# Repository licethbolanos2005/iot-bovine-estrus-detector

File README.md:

# 🐄 IoT Bovine Estrus Detector

Prototipo IoT basado en tecnología **LoRa** para la detección temprana del celo en bovinos mediante el monitoreo continuo de variables fisiológicas y comportamentales.

> Proyecto integrador — Ingeniería Electrónica  
> Unidad Central del Valle del Cauca - Semestre 8
> Autores: Liceth Bolaños, Santiago Albarracin, Arlyn Cardozo, Samuel Guevara

---

## 📋 Descripción general

El sistema integra un nodo transmisor montado en un chaleco portador adaptado al animal, el cual captura temperatura corporal, actividad motora, frecuencia respiratoria y eventos de monta. Los datos son procesados por un **ESP32 LoRa V3 (ESP32-S3 + SX1262)**, almacenados localmente en MicroSD con marca temporal RTC y transmitidos de forma inalámbrica al nodo receptor, donde son visualizados en **Grafana** a través de **InfluxDB**.

---

## 📁 Estructura del repositorio

```
iot-bovine-estrus-detector/
│
├── Board/                  # Diseño final de la PCB (KiCad)
│   └── ...                 # Archivos .kicad_pcb, .kicad_sch, Gerbers
│
├── Box/                    # Diseño de la caja de protección (impresión 3D)
│   └── ...                 # Archivos .ipt
│
├── Receiver_Code/          # Firmware del nodo receptor
│   └── ...                 # Código ESP32 — recepción LoRa, envío a InfluxDB
│
├── Schematic/              # Esquemático electrónico del sistema
│   └── ...                 # Archivos .kicad_sch
│
├── Transmitter_Code/       # Firmware del nodo transmisor
│   └── ...                 # Código ESP32 — sensores, LoRa, MicroSD, RTC, Web server
│
└── README.md
```

---

## ⚙️ Hardware utilizado

| Componente | Función |
|---|---|
| WiFi LoRa 32 V3 (ESP32-S3 + SX1262) | Unidad central de procesamiento y comunicación |
| DS18B20 | Medición de temperatura corporal |
| MPU6050 | Actividad motora y frecuencia respiratoria |
| FSR (Force Sensitive Resistor) | Detección de eventos de monta |
| INA219 | Monitoreo de consumo energético |
| DS3231 (RTC) | Registro temporal de datos |
| Módulo MicroSD TF | Almacenamiento local de datos |
| Batería LiPo 3.7V | Alimentación del sistema |

---

## 📡 Parámetros de comunicación LoRa

| Parámetro | Valor |
|---|---|
| Banda | 915 MHz (ISM) |
| Spreading Factor | 7 |
| Bandwidth | 125 kHz |
| Coding Rate | 5 |
| Sync Word | 0x12 |
| Potencia TX | 14 dBm |

---

## 🖥️ Arquitectura del sistema

```
[Sensores] → [ESP32 Transmisor] → [LoRa 915 MHz] → [ESP32 Receptor]
                    ↓                                        ↓
               [MicroSD + RTC]                        [InfluxDB → Grafana]
                    ↓
             [Servidor Web Embebido / OTA]
```

---

## 🚀 Primeros pasos

### Requisitos

- [Arduino IDE](https://www.arduino.cc/en/software) o [PlatformIO](https://platformio.org/)
- Placa: **Heltec WiFi LoRa 32 V3**
- Librerías necesarias:
  - `RadioLib`
  - `OneWire` + `DallasTemperature`
  - `MPU6050`
  - `RTClib`
  - `SD`
  - `INA219`
  - `ArduinoJson`
  - `ESPAsyncWebServer`

### Cargar firmware transmisor

1. Abre `Transmitter_Code/` en Arduino IDE o PlatformIO.
2. Configura los parámetros de red WiFi y LoRa en el archivo de configuración.
3. Compila y carga en la placa ESP32 del nodo transmisor.

### Cargar firmware receptor

1. Abre `Receiver_Code/` en Arduino IDE o PlatformIO.
2. Configura la dirección IP de InfluxDB y las credenciales de red.
3. Compila y carga en la placa ESP32 del nodo receptor.

---

## 📊 Visualización

Los datos son enviados a **InfluxDB** y visualizados en tiempo real mediante **Grafana**, donde se monitorean:

- Temperatura corporal (°C)
- Magnitud de aceleración (actividad motora)
- Frecuencia respiratoria
- Consumo energético (mA)
- Estado de celo (algoritmo de detección)
- Eventos de monta (FSR)
- Calidad del enlace LoRa (RSSI / SNR)

---

## 🌐 Servidor web embebido

El nodo transmisor implementa un servidor web accesible en la red local mediante:

```
http://boviot.local
```

Desde la interfaz web es posible:
- Visualizar variables fisiológicas en tiempo real
- Configurar parámetros de red WiFi
- Actualizar el firmware de forma inalámbrica (**OTA**)

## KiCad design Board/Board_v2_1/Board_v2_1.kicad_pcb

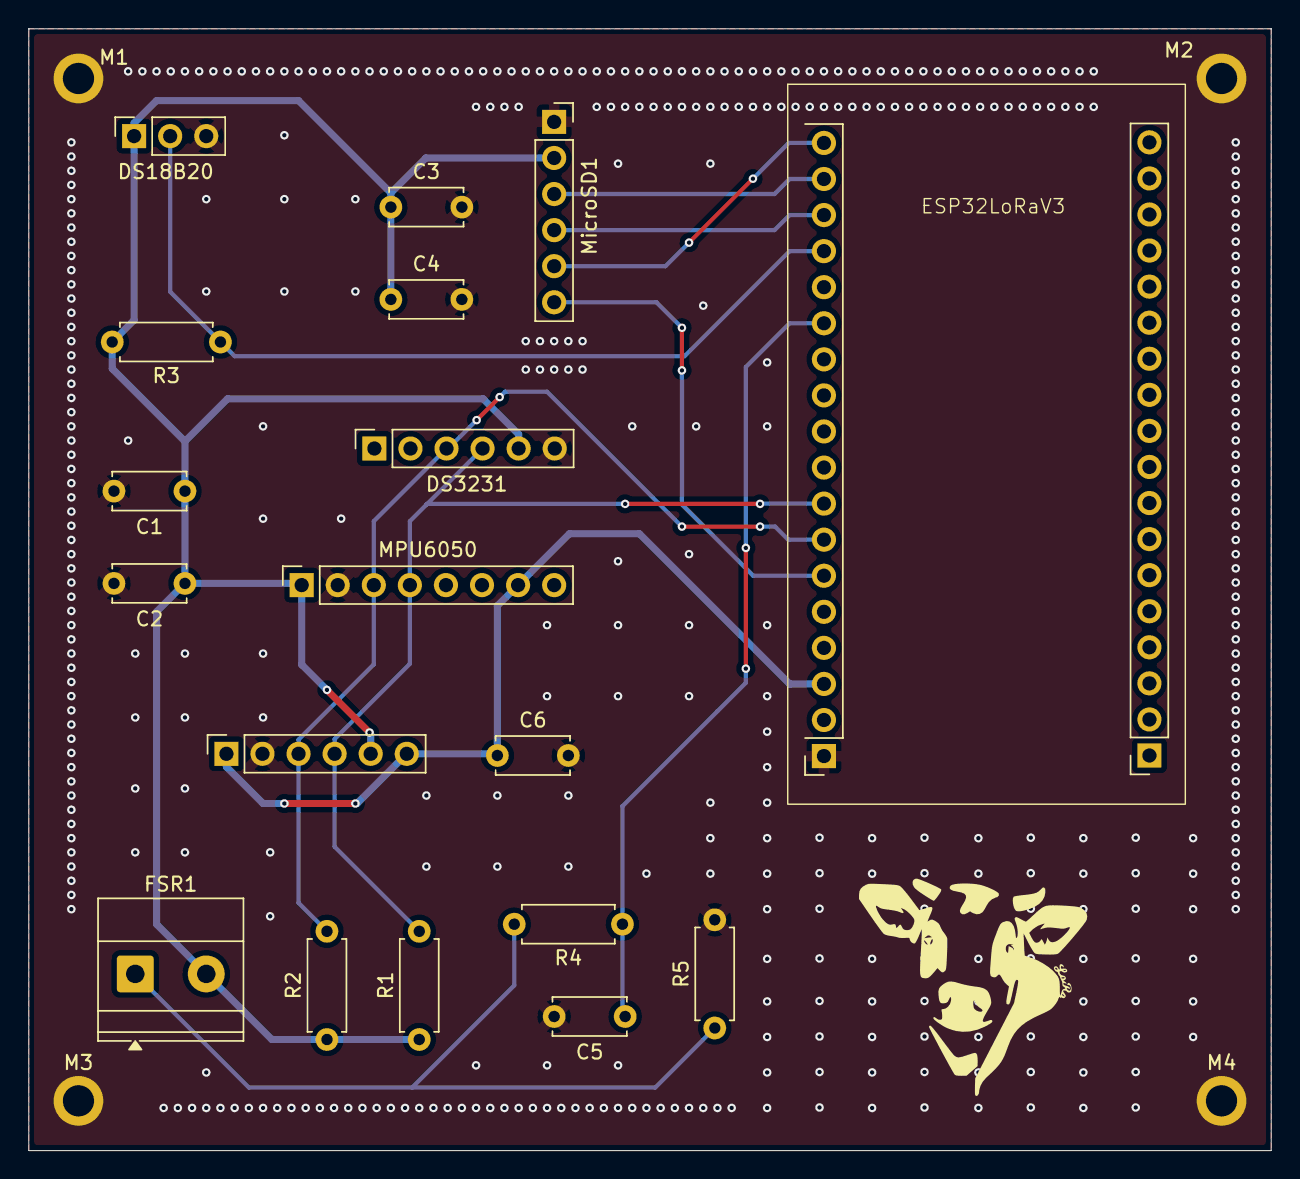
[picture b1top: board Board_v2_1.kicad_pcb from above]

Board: 2 copper layers, 87.5 x 79.0 mm, 22 parts (0 on the bottom side), 12 nets.

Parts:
C1, C3, C5, C6: 100nf; C_Disc_D5.0mm_W2.5mm_P5.00mm
C2, C4: 10uf; C_Disc_D5.0mm_W2.5mm_P5.00mm
DS18B20: Conn_01x03; PinSocket_1x03_P2.54mm_Vertical
DS3231: PinSocket_1x06_P2.54mm_Vertical
ESP32LoRaV3: ESP32 Lora V3
FSR1: Conn_01x02; TerminalBlock_Phoenix_MKDS-1,5-2_1x02_P5.00mm_Horizontal
INA219: PinSocket_1x06_P2.54mm_Vertical
M1, M2, M3, M4: MountingHole_2.2mm_M2_ISO7380_Pad
MPU6050: Conn_01x08; PinSocket_1x08_P2.54mm_Vertical
MicroSD1: PinSocket_1x06_P2.54mm_Vertical
R1, R2, R3: 4.7K; R_Axial_DIN0207_L6.3mm_D2.5mm_P7.62mm_Horizontal
R4: 10K; R_Axial_DIN0207_L6.3mm_D2.5mm_P7.62mm_Horizontal
R5: 50K; R_Axial_DIN0207_L6.3mm_D2.5mm_P7.62mm_Horizontal

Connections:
+3V3: C6.1, ESP32LoRaV3.3 (3V3), INA219.1, INA219.6, MPU6050.7
/CS: ESP32LoRaV3.6 (GPIO45), MicroSD1.6
/FSR: C5.1, ESP32LoRaV3.13 (GPIO2), R4.1
/MISO: ESP32LoRaV3.17 (GPIO6), MicroSD1.3
/MOSI: ESP32LoRaV3.16 (GPIO5), MicroSD1.4
/SCK: ESP32LoRaV3.18 (GPIO7), MicroSD1.5
/SCL: DS3231.3, ESP32LoRaV3.7 (GPIO42), INA219.3, MPU6050.3, R2.2
/SDA: DS3231.4, ESP32LoRaV3.8 (GPIO41), INA219.4, MPU6050.4, R1.2
/TEMP: DS18B20.2, ESP32LoRaV3.15 (GPIO4), R3.1
GND: C1.2, C2.2, C3.2, C4.2, C5.2, C6.2, DS18B20.3, DS3231.6, ESP32LoRaV3.1 (GND), INA219.2, M1.1, M2.2, M3.2, M4.4, MPU6050.2, MicroSD1.1, R5.2
unnamed: FSR1.1, R4.2, R5.1
VIN-: C1.1, C2.1, C3.1, C4.1, DS18B20.1, DS3231.5, FSR1.2, INA219.5, MPU6050.1, MicroSD1.2, R1.1, R2.1, R3.2

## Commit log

2026-03-22 Primer esquemático del sistema IoT propuesto
    Primer esquemático del sistema IoT propuesto
2026-03-23 Code_v1_1
    Primera versión del código
2026-04-07 Corregí el bloque del acelerómetro
    Corregí el bloque del acelerómetro
2026-04-07 Code_v1_2
    Código con la corrección del acelerómetro agregado
2026-04-14 Modifiqué el esquemático de acuerdo a los nuevos cambios con el módulo ESP32 LoRa V3. Hice primer avance de pcb
2026-04-18 Se añadieron los planos de tierra y se realizaron vias stitching
2026-04-20 Se sube el código con la última actualización donde se cambia la esp32 y el módulo Ra-02 por 2 HiLetgo ESP32 V3 LoRa V3 SX1262
2026-04-22 Versión final de pcb
2026-05-13 Se agrega el diseño de la caja para la PCB del nodo sensor
2026-05-23 Añadí primera versión del código del receptor, funcionando correctamente la recepción de datos
2026-05-23 Agregué versión completa del código del transmisor, con los sensores funcionando correctamente
2026-05-23 Se integró un web server para el receptor
2026-05-23 Se integró un web server para el transmisor
2026-05-23 Se agregó la variable de frecuencia respiratoria
2026-06-02 Se agregan versiones finales de código de receptor y código de transmisor
